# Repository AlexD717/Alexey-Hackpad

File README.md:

# Alexey-Hackpad

Custom macro pad with 7 keys, an encoder, and an LED light bar, using KMK firmware.

## Features

- 7 keys
  - One key to switch between layers, 6 for macros
- EC11 Rotary encoder with push switch
- LED Light bar displaying custom status
- Custom 2-layer PCB

## CAD Model

### Assembly

### Render

## PCB Design

This PCB was made in KiCad.

### Schematic

### PCB

## Firware

This hackpad uses KMK for its firmware.

- One switch is in charge of switching layers
- Other six keys act as custom macros
- Rotary encoder controls volume and plays/stops music

## BOM

- Seeed XIAO RP2040
- 7x Cherry MX Switches
- 7x DSA Keycaps
- 1x EC11 Rotary encoder
- 1x Rotary enoder knob (3d-printed)
- 4x SK6812 MINI-E LEDs
- 8x Through-hole 1N4148 Diodes
- 4x M3x5x4 Heatset inserts
- 4x M3x16mm screws
- 1x Case (3, 3d-printed parts)

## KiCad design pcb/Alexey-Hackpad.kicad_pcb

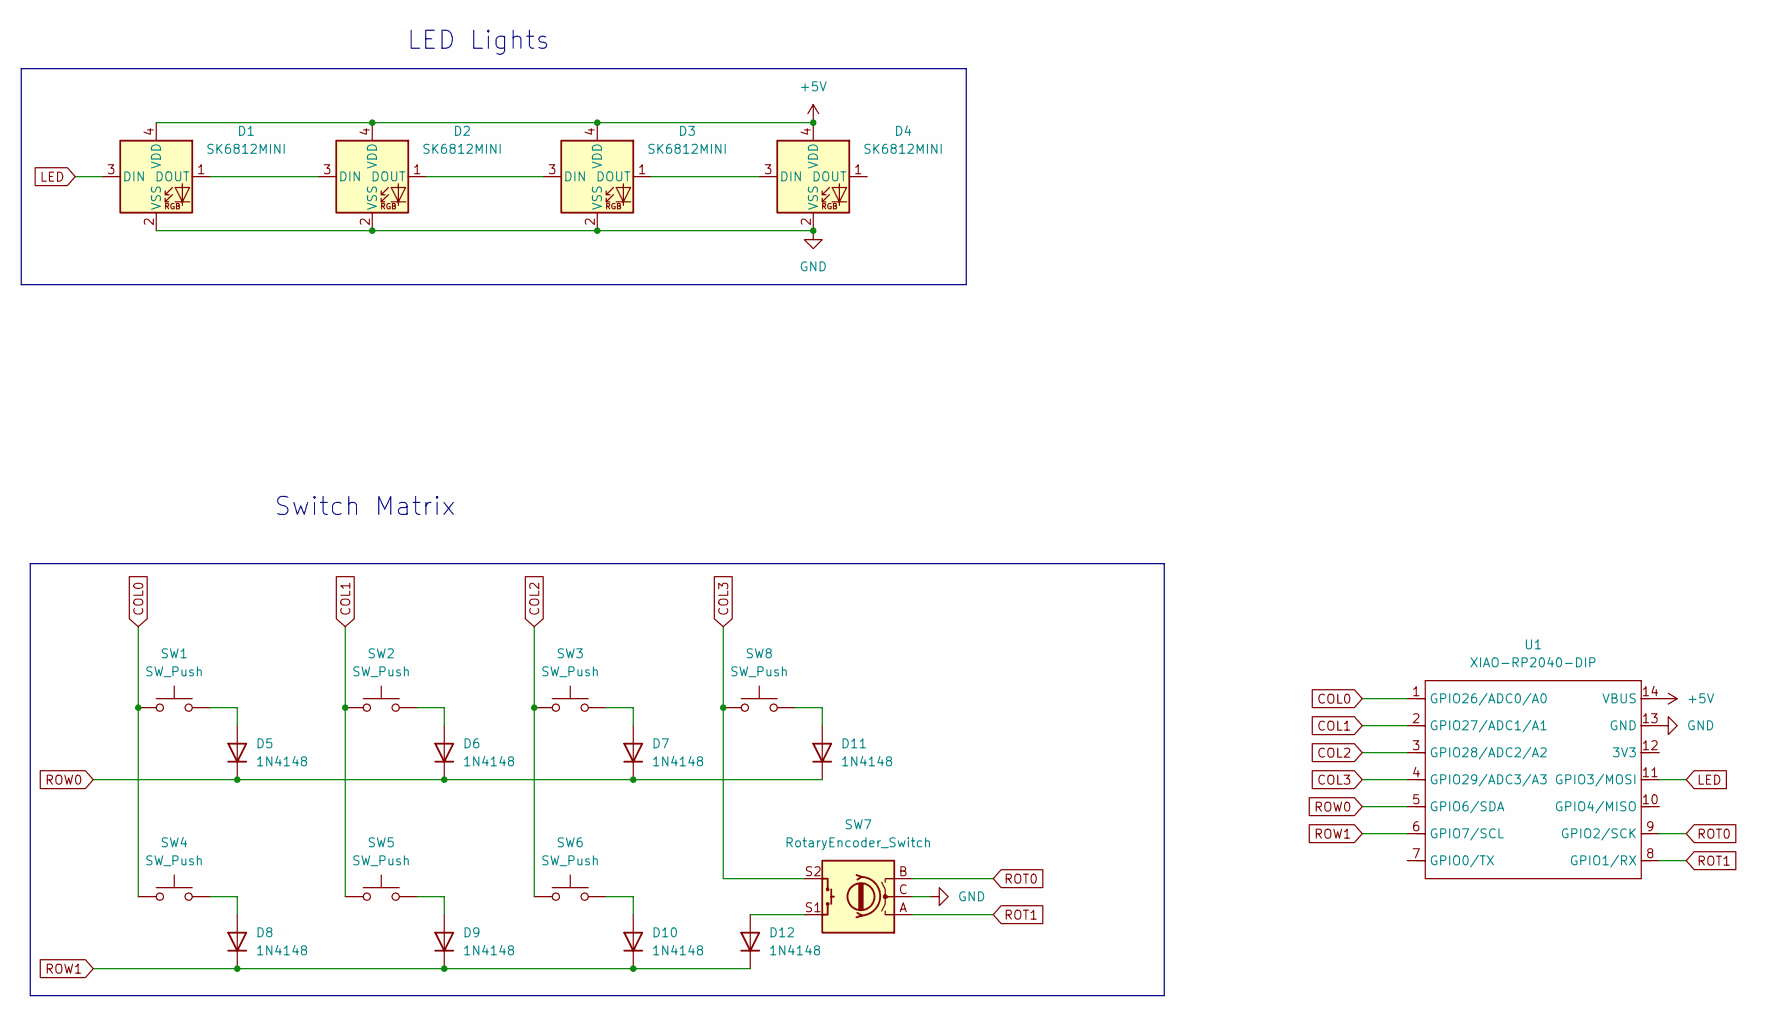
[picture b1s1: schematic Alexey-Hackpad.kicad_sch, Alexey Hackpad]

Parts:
D1, D2, D3, D4: SK6812MINI; LED_SK6812MINI_PLCC4_3.5x3.5mm_P1.75mm
D5, D6, D7, D8, D9, D10, D11, D12: 1N4148; D_DO-35_SOD27_P7.62mm_Horizontal
SW1, SW2, SW3, SW4, SW5, SW6, SW8: SW_Push; SW_Cherry_MX_1.00u_PCB
SW7: RotaryEncoder_Switch; RotaryEncoder_Alps_EC11E-Switch_Vertical_H20mm
U1: XIAO-RP2040-DIP

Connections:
+5V: D1.4 (VDD), D2.4 (VDD), D3.4 (VDD), D4.4 (VDD), U1.14 (VBUS)
COL0: SW1.1, SW4.1, U1.1 (GPIO26/ADC0/A0)
COL1: SW2.1, SW5.1, U1.2 (GPIO27/ADC1/A1)
COL2: SW3.1, SW6.1, U1.3 (GPIO28/ADC2/A2)
COL3: SW7.S2, SW8.1, U1.4 (GPIO29/ADC3/A3)
GND: D1.2 (VSS), D2.2 (VSS), D3.2 (VSS), D4.2 (VSS), SW7.C, U1.13 (GND)
LED: D1.3 (DIN), U1.11 (GPIO3/MOSI)
unnamed: D1.1 (DOUT), D2.3 (DIN)
unnamed: D2.1 (DOUT), D3.3 (DIN)
unnamed: D3.1 (DOUT), D4.3 (DIN)
unnamed: D5.2 (A), SW1.2
unnamed: D6.2 (A), SW2.2
unnamed: D7.2 (A), SW3.2
unnamed: D8.2 (A), SW4.2
unnamed: D9.2 (A), SW5.2
unnamed: D10.2 (A), SW6.2
unnamed: D11.2 (A), SW8.2
unnamed: D12.2 (A), SW7.S1
ROT0: SW7.B, U1.9 (GPIO2/SCK)
ROT1: SW7.A, U1.8 (GPIO1/RX)
ROW0: D5.1 (K), D6.1 (K), D7.1 (K), D11.1 (K), U1.5 (GPIO6/SDA)
ROW1: D8.1 (K), D9.1 (K), D10.1 (K), D12.1 (K), U1.6 (GPIO7/SCL)

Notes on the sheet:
LED Lights
Switch Matrix

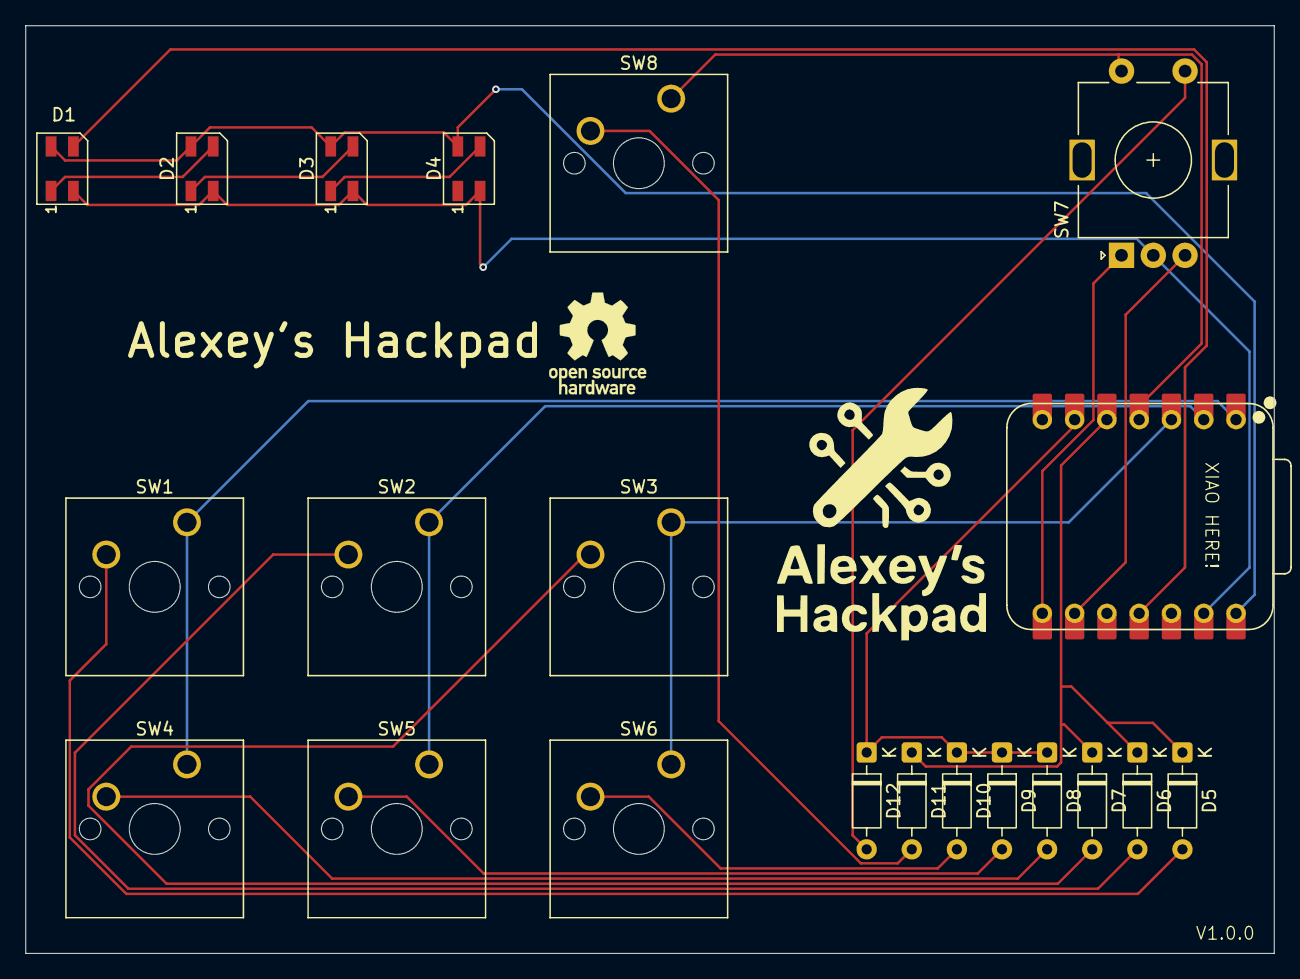
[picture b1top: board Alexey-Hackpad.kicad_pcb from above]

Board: 2 copper layers, 98.2 x 73.0 mm, 21 parts (0 on the bottom side), 22 nets.

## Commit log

2025-07-04 Update README.md to Include Features and BOM
2025-07-04 Images Uploaded
2025-07-04 Simple Firmware
2025-07-04 CAD Model
2025-07-04 PCB Designs
2025-07-04 Production Data
